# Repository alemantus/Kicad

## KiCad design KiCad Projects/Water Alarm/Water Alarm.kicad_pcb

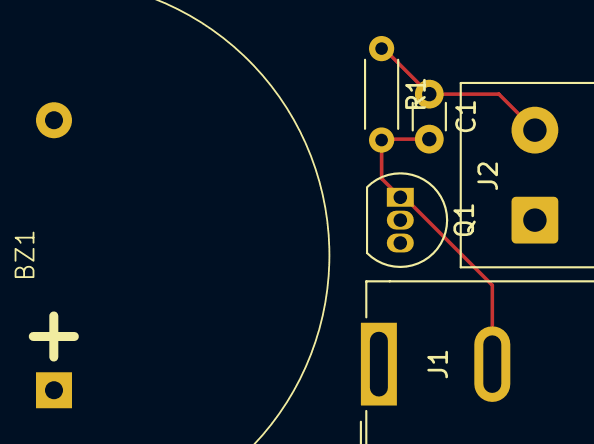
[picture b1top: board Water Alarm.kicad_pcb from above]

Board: 2 copper layers, 6 parts (0 on the bottom side), 3 nets.

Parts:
BZ1: Buzzer; Buzzer_D30mm_H20mm_p15mm_668-1204-ND_AI-3035-TWT-3V-R
C1: 1nF; C_Disc_D3.0mm_W1.6mm_P2.50mm
J1: Jack-DC; BarrelJack_GCT_DCJ200-10-A_Horizontal
J2: Screw_Terminal_01x02; TerminalBlock_Phoenix_PT-1,5-2-5.0-H_1x02_P5.00mm_Horizontal
Q1: 2N7000; TO-92_Inline
R1: 10M; R_Axial_DIN0204_L3.6mm_D1.6mm_P5.08mm_Horizontal

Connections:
/Gate: C1.1, J2.2, Q1.2 (G), R1.1
GND: C1.2, J1.2, Q1.1 (S), R1.2
VCC: BZ1.1 (+), J1.1, J2.1
